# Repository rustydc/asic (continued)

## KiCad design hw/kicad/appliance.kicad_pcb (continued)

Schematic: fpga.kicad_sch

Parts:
J_BMC_NET: BMC Ethernet; RJ45_MAGJACK
J_HOST: SlimSAS 8i host cable; SLIMSAS_8I
J_SFP: SFP+ cage; SFP_CAGE
U_BMC: BMC SoC; BGA_BMC_21x21
U_CLK: Si5345; QFN64_9x9
U_FPGA: FPGA; FFVB676_26x26_P1.0

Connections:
BMC_ETH0_N: J_BMC_NET.2, U_BMC.2
BMC_ETH0_P: J_BMC_NET.1, U_BMC.1
BMC_ETH1_N: J_BMC_NET.4, U_BMC.4
BMC_ETH1_P: J_BMC_NET.3, U_BMC.3
BMC_ETH2_N: J_BMC_NET.6, U_BMC.6
BMC_ETH2_P: J_BMC_NET.5, U_BMC.5
BMC_ETH3_N: J_BMC_NET.8, U_BMC.8
BMC_ETH3_P: J_BMC_NET.7, U_BMC.7
DDR4_ADDR_CMD0: U_FPGA.D11; also elsewhere on the board
DDR4_ADDR_CMD1: U_FPGA.D12; also elsewhere on the board
DDR4_ADDR_CMD2: U_FPGA.D13; also elsewhere on the board
DDR4_ADDR_CMD3: U_FPGA.D14; also elsewhere on the board
DDR4_ADDR_CMD4: U_FPGA.D15; also elsewhere on the board
DDR4_ADDR_CMD5: U_FPGA.D16; also elsewhere on the board
DDR4_ADDR_CMD6: U_FPGA.D17; also elsewhere on the board
DDR4_ADDR_CMD7: U_FPGA.D18; also elsewhere on the board
DDR4_ADDR_CMD8: U_FPGA.D19; also elsewhere on the board
DDR4_ADDR_CMD9: U_FPGA.D20; also elsewhere on the board
DDR4_ADDR_CMD10: U_FPGA.D21; also elsewhere on the board
DDR4_ADDR_CMD11: U_FPGA.D22; also elsewhere on the board
DDR4_ADDR_CMD12: U_FPGA.D23; also elsewhere on the board
DDR4_ADDR_CMD13: U_FPGA.D24; also elsewhere on the board
DDR4_ADDR_CMD14: U_FPGA.D25; also elsewhere on the board
DDR4_ADDR_CMD15: U_FPGA.D26; also elsewhere on the board
DDR4_ADDR_CMD16: U_FPGA.E3; also elsewhere on the board
DDR4_ADDR_CMD17: U_FPGA.E4; also elsewhere on the board
DDR4_ADDR_CMD18: U_FPGA.E5; also elsewhere on the board
DDR4_ADDR_CMD19: U_FPGA.E6; also elsewhere on the board
DDR4_ADDR_CMD20: U_FPGA.E7; also elsewhere on the board
DDR4_ADDR_CMD21: U_FPGA.E8; also elsewhere on the board
DDR4_ADDR_CMD22: U_FPGA.E9; also elsewhere on the board
DDR4_ADDR_CMD23: U_FPGA.E10; also elsewhere on the board
DDR4_ADDR_CMD24: U_FPGA.E11; also elsewhere on the board
DDR4_ADDR_CMD25: U_FPGA.E12; also elsewhere on the board
DDR4_ADDR_CMD26: U_FPGA.E13; also elsewhere on the board
DDR4_ADDR_CMD27: U_FPGA.E14; also elsewhere on the board
DDR4_CK_N: U_FPGA.E16; also elsewhere on the board
DDR4_CK_P: U_FPGA.E15; also elsewhere on the board
DDR4_CTRL0: U_FPGA.E17; also elsewhere on the board
DDR4_CTRL1: U_FPGA.E18; also elsewhere on the board
DDR4_CTRL2: U_FPGA.E19; also elsewhere on the board
DDR4_CTRL3: U_FPGA.E20; also elsewhere on the board
DDR4_CTRL4: U_FPGA.E21; also elsewhere on the board
DDR4_CTRL5: U_FPGA.E22; also elsewhere on the board
DDR4_DM0: U_FPGA.D3; also elsewhere on the board
DDR4_DM1: U_FPGA.D4; also elsewhere on the board
DDR4_DM2: U_FPGA.D5; also elsewhere on the board
DDR4_DM3: U_FPGA.D6; also elsewhere on the board
DDR4_DM4: U_FPGA.D7; also elsewhere on the board
DDR4_DM5: U_FPGA.D8; also elsewhere on the board
DDR4_DM6: U_FPGA.D9; also elsewhere on the board
DDR4_DM7: U_FPGA.D10; also elsewhere on the board
DDR4_DQ0: U_FPGA.A1; also elsewhere on the board
DDR4_DQ1: U_FPGA.A2; also elsewhere on the board
DDR4_DQ2: U_FPGA.A3; also elsewhere on the board
DDR4_DQ3: U_FPGA.A4; also elsewhere on the board
DDR4_DQ4: U_FPGA.A5; also elsewhere on the board
DDR4_DQ5: U_FPGA.A6; also elsewhere on the board
DDR4_DQ6: U_FPGA.A7; also elsewhere on the board
DDR4_DQ7: U_FPGA.A8; also elsewhere on the board
DDR4_DQ8: U_FPGA.A9; also elsewhere on the board
DDR4_DQ9: U_FPGA.A10; also elsewhere on the board
DDR4_DQ10: U_FPGA.A11; also elsewhere on the board
DDR4_DQ11: U_FPGA.A12; also elsewhere on the board
DDR4_DQ12: U_FPGA.A13; also elsewhere on the board
DDR4_DQ13: U_FPGA.A14; also elsewhere on the board
DDR4_DQ14: U_FPGA.A15; also elsewhere on the board
DDR4_DQ15: U_FPGA.A16; also elsewhere on the board
DDR4_DQ16: U_FPGA.A17; also elsewhere on the board
DDR4_DQ17: U_FPGA.A18; also elsewhere on the board
DDR4_DQ18: U_FPGA.A19; also elsewhere on the board
DDR4_DQ19: U_FPGA.A20; also elsewhere on the board
DDR4_DQ20: U_FPGA.A21; also elsewhere on the board
DDR4_DQ21: U_FPGA.A22; also elsewhere on the board
DDR4_DQ22: U_FPGA.A23; also elsewhere on the board
DDR4_DQ23: U_FPGA.A24; also elsewhere on the board
DDR4_DQ24: U_FPGA.A25; also elsewhere on the board
DDR4_DQ25: U_FPGA.A26; also elsewhere on the board
DDR4_DQ26: U_FPGA.B1; also elsewhere on the board
DDR4_DQ27: U_FPGA.B2; also elsewhere on the board
DDR4_DQ28: U_FPGA.B3; also elsewhere on the board
DDR4_DQ29: U_FPGA.B4; also elsewhere on the board
DDR4_DQ30: U_FPGA.B5; also elsewhere on the board
DDR4_DQ31: U_FPGA.B6; also elsewhere on the board
DDR4_DQ32: U_FPGA.B7; also elsewhere on the board
DDR4_DQ33: U_FPGA.B8; also elsewhere on the board
DDR4_DQ34: U_FPGA.B9; also elsewhere on the board
DDR4_DQ35: U_FPGA.B10; also elsewhere on the board
DDR4_DQ36: U_FPGA.B11; also elsewhere on the board
DDR4_DQ37: U_FPGA.B12; also elsewhere on the board
DDR4_DQ38: U_FPGA.B13; also elsewhere on the board
DDR4_DQ39: U_FPGA.B14; also elsewhere on the board
DDR4_DQ40: U_FPGA.B15; also elsewhere on the board
DDR4_DQ41: U_FPGA.B16; also elsewhere on the board
DDR4_DQ42: U_FPGA.B17; also elsewhere on the board
DDR4_DQ43: U_FPGA.B18; also elsewhere on the board
DDR4_DQ44: U_FPGA.B19; also elsewhere on the board
DDR4_DQ45: U_FPGA.B20; also elsewhere on the board
DDR4_DQ46: U_FPGA.B21; also elsewhere on the board
DDR4_DQ47: U_FPGA.B22; also elsewhere on the board
DDR4_DQ48: U_FPGA.B23; also elsewhere on the board
DDR4_DQ49: U_FPGA.B24; also elsewhere on the board
DDR4_DQ50: U_FPGA.B25; also elsewhere on the board
DDR4_DQ51: U_FPGA.B26; also elsewhere on the board
DDR4_DQ52: U_FPGA.C1; also elsewhere on the board
DDR4_DQ53: U_FPGA.C2; also elsewhere on the board
DDR4_DQ54: U_FPGA.C3; also elsewhere on the board
DDR4_DQ55: U_FPGA.C4; also elsewhere on the board
DDR4_DQ56: U_FPGA.C5; also elsewhere on the board
DDR4_DQ57: U_FPGA.C6; also elsewhere on the board
DDR4_DQ58: U_FPGA.C7; also elsewhere on the board
DDR4_DQ59: U_FPGA.C8; also elsewhere on the board
DDR4_DQ60: U_FPGA.C9; also elsewhere on the board
DDR4_DQ61: U_FPGA.C10; also elsewhere on the board
DDR4_DQ62: U_FPGA.C11; also elsewhere on the board
DDR4_DQ63: U_FPGA.C12; also elsewhere on the board
DDR4_DQS0_N: U_FPGA.C14; also elsewhere on the board
DDR4_DQS0_P: U_FPGA.C13; also elsewhere on the board
DDR4_DQS1_N: U_FPGA.C16; also elsewhere on the board
DDR4_DQS1_P: U_FPGA.C15; also elsewhere on the board
DDR4_DQS2_N: U_FPGA.C18; also elsewhere on the board
DDR4_DQS2_P: U_FPGA.C17; also elsewhere on the board
DDR4_DQS3_N: U_FPGA.C20; also elsewhere on the board
DDR4_DQS3_P: U_FPGA.C19; also elsewhere on the board
DDR4_DQS4_N: U_FPGA.C22; also elsewhere on the board
DDR4_DQS4_P: U_FPGA.C21; also elsewhere on the board
DDR4_DQS5_N: U_FPGA.C24; also elsewhere on the board
DDR4_DQS5_P: U_FPGA.C23; also elsewhere on the board
DDR4_DQS6_N: U_FPGA.C26; also elsewhere on the board
DDR4_DQS6_P: U_FPGA.C25; also elsewhere on the board
DDR4_DQS7_N: U_FPGA.D2; also elsewhere on the board
DDR4_DQS7_P: U_FPGA.D1; also elsewhere on the board
FAN_0_PWM: U_BMC.9; also elsewhere on the board
FAN_0_TACH: U_BMC.10; also elsewhere on the board
FAN_1_PWM: U_BMC.11; also elsewhere on the board
FAN_1_TACH: U_BMC.12; also elsewhere on the board
FAN_2_PWM: U_BMC.13; also elsewhere on the board
FAN_2_TACH: U_BMC.14; also elsewhere on the board
FAN_3_PWM: U_BMC.15; also elsewhere on the board
FAN_3_TACH: U_BMC.16; also elsewhere on the board
FAN_4_PWM: U_BMC.17; also elsewhere on the board
FAN_4_TACH: U_BMC.18; also elsewhere on the board
FAN_5_PWM: U_BMC.19; also elsewhere on the board
FAN_5_TACH: U_BMC.20; also elsewhere on the board
GND: J_BMC_NET.10, J_BMC_NET.11, J_BMC_NET.12, J_HOST.37, J_HOST.38, J_HOST.39, J_HOST.40, J_HOST.41, J_HOST.42, J_HOST.43, J_HOST.44, J_HOST.45, J_HOST.46, J_HOST.47, J_HOST.48, J_HOST.49, J_HOST.50, J_HOST.51, J_HOST.52, J_HOST.53, J_HOST.54, J_SFP.13, J_SFP.14, J_SFP.15, J_SFP.16, U_BMC.28, U_BMC.29, U_CLK.2, U_FPGA.AA3, U_FPGA.AA5, U_FPGA.AA7, U_FPGA.AA9, U_FPGA.AA11, U_FPGA.AA13, U_FPGA.AA15, U_FPGA.AA17, U_FPGA.AA19, U_FPGA.AA21, U_FPGA.AA23, U_FPGA.AB4, U_FPGA.AB6, U_FPGA.AB8, U_FPGA.AB10, U_FPGA.AB12, U_FPGA.AB14, U_FPGA.AB16, U_FPGA.AB18, U_FPGA.AB20, U_FPGA.AB22, U_FPGA.AB24, U_FPGA.AC25, U_FPGA.AD26, U_FPGA.AE1, U_FPGA.AE17, U_FPGA.AE19, U_FPGA.AE21, U_FPGA.AE23, U_FPGA.AE25, U_FPGA.AF2, U_FPGA.AF26, U_FPGA.E23, U_FPGA.F4, U_FPGA.F6, U_FPGA.F8, U_FPGA.F10, U_FPGA.F12, U_FPGA.F14, U_FPGA.F16, U_FPGA.F18, U_FPGA.F20, U_FPGA.F22, U_FPGA.F24, U_FPGA.G3, U_FPGA.G5, U_FPGA.G7, U_FPGA.G9, U_FPGA.G11, U_FPGA.G13, U_FPGA.G15, U_FPGA.G17, U_FPGA.G19, U_FPGA.G21, U_FPGA.G23, U_FPGA.H4, U_FPGA.H6, U_FPGA.H8, U_FPGA.H10, U_FPGA.H12, U_FPGA.H14, U_FPGA.H16, U_FPGA.H18, U_FPGA.H20, U_FPGA.H22, U_FPGA.H24, U_FPGA.J3, U_FPGA.J5, U_FPGA.J7, U_FPGA.J9, U_FPGA.J11, U_FPGA.J13, U_FPGA.J15, U_FPGA.J17, U_FPGA.J19, U_FPGA.J21, U_FPGA.J23, U_FPGA.K4, U_FPGA.K6, U_FPGA.K8, U_FPGA.K10, U_FPGA.K12, U_FPGA.K14, U_FPGA.K16, U_FPGA.K18, U_FPGA.K20, U_FPGA.K22, U_FPGA.K24, U_FPGA.L3, U_FPGA.L5, U_FPGA.L7, U_FPGA.L9, U_FPGA.L11, U_FPGA.L13, U_FPGA.L15, U_FPGA.L17, U_FPGA.L19, U_FPGA.L21, U_FPGA.L23, U_FPGA.M4, U_FPGA.M6, U_FPGA.M8, U_FPGA.M10, U_FPGA.M12, U_FPGA.M14, U_FPGA.M16, U_FPGA.M18, U_FPGA.M20, U_FPGA.M22, U_FPGA.M24, U_FPGA.N3, U_FPGA.N5, U_FPGA.N7, U_FPGA.N9, U_FPGA.N11, U_FPGA.N13, U_FPGA.N15, U_FPGA.N17, U_FPGA.N19, U_FPGA.N21, U_FPGA.N23, U_FPGA.P4, U_FPGA.P6, U_FPGA.P8, U_FPGA.P10, U_FPGA.P12, U_FPGA.P14, U_FPGA.P16, U_FPGA.P18, U_FPGA.P20, U_FPGA.P22, U_FPGA.P24, U_FPGA.R3, U_FPGA.R5, U_FPGA.R7, U_FPGA.R9, U_FPGA.R11, U_FPGA.R13, U_FPGA.R15, U_FPGA.R17, U_FPGA.R19, U_FPGA.R21, U_FPGA.R23, U_FPGA.T4, U_FPGA.T6, U_FPGA.T8, U_FPGA.T10, U_FPGA.T12, U_FPGA.T14, U_FPGA.T16, U_FPGA.T18, U_FPGA.T20, U_FPGA.T22, U_FPGA.T24, U_FPGA.U3, U_FPGA.U5, U_FPGA.U7, U_FPGA.U9, U_FPGA.U11, U_FPGA.U13, U_FPGA.U15, U_FPGA.U17, U_FPGA.U19, U_FPGA.U21, U_FPGA.U23, U_FPGA.V4, U_FPGA.V6, U_FPGA.V8, U_FPGA.V10, U_FPGA.V12, U_FPGA.V14, U_FPGA.V16, U_FPGA.V18, U_FPGA.V20, U_FPGA.V22, U_FPGA.V24, U_FPGA.W3, U_FPGA.W5, U_FPGA.W7, U_FPGA.W9, U_FPGA.W11, U_FPGA.W13, U_FPGA.W15, U_FPGA.W17, U_FPGA.W19, U_FPGA.W21, U_FPGA.W23, U_FPGA.Y4, U_FPGA.Y6, U_FPGA.Y8, U_FPGA.Y10, U_FPGA.Y12, U_FPGA.Y14, U_FPGA.Y16, U_FPGA.Y18, U_FPGA.Y20, U_FPGA.Y22, U_FPGA.Y24; also elsewhere on the board
JTAG_TCK: U_FPGA.AC24; also elsewhere on the board
JTAG_TDI_FPGA: U_FPGA.AD2
JTAG_TDO_FPGA: U_FPGA.AD3; also elsewhere on the board
JTAG_TMS: U_FPGA.AD1; also elsewhere on the board
JTAG_TRST: U_FPGA.AD4; also elsewhere on the board
LINK0_CLOCK: U_FPGA.AA26; also elsewhere on the board
LINK0_DATA0: U_FPGA.E26; also elsewhere on the board
LINK0_DATA1: U_FPGA.E25; also elsewhere on the board
LINK0_DATA2: U_FPGA.F26; also elsewhere on the board
LINK0_DATA3: U_FPGA.F25; also elsewhere on the board
LINK0_DATA4: U_FPGA.G26; also elsewhere on the board
LINK0_DATA5: U_FPGA.G25; also elsewhere on the board
LINK0_DATA6: U_FPGA.H26; also elsewhere on the board
LINK0_DATA7: U_FPGA.H25; also elsewhere on the board
LINK0_DATA8: U_FPGA.J26; also elsewhere on the board
LINK0_DATA9: U_FPGA.J25; also elsewhere on the board
LINK0_DATA10: U_FPGA.K26; also elsewhere on the board
LINK0_DATA11: U_FPGA.K25; also elsewhere on the board
LINK0_DATA12: U_FPGA.L26; also elsewhere on the board
LINK0_DATA13: U_FPGA.L25; also elsewhere on the board
LINK0_DATA14: U_FPGA.M26; also elsewhere on the board
LINK0_DATA15: U_FPGA.M25; also elsewhere on the board
LINK0_DATA16: U_FPGA.N26; also elsewhere on the board
LINK0_DATA17: U_FPGA.N25; also elsewhere on the board
LINK0_DATA18: U_FPGA.P26; also elsewhere on the board
LINK0_DATA19: U_FPGA.P25; also elsewhere on the board
LINK0_DATA20: U_FPGA.R26; also elsewhere on the board
LINK0_DATA21: U_FPGA.R25; also elsewhere on the board
LINK0_DATA22: U_FPGA.T26; also elsewhere on the board
LINK0_DATA23: U_FPGA.T25; also elsewhere on the board
LINK0_DATA24: U_FPGA.U26; also elsewhere on the board
LINK0_DATA25: U_FPGA.U25; also elsewhere on the board
LINK0_DATA26: U_FPGA.V26; also elsewhere on the board
LINK0_DATA27: U_FPGA.V25; also elsewhere on the board
LINK0_DATA28: U_FPGA.W26; also elsewhere on the board
LINK0_DATA29: U_FPGA.W25; also elsewhere on the board
LINK0_DATA30: U_FPGA.Y26; also elsewhere on the board
LINK0_DATA31: U_FPGA.Y25; also elsewhere on the board
LINK0_READY_BACK: U_FPGA.AB26; also elsewhere on the board
LINK0_SOF: U_FPGA.AB25; also elsewhere on the board
LINK0_VALID: U_FPGA.AA25; also elsewhere on the board
LINK10_CLOCK: U_FPGA.AA1; also elsewhere on the board
LINK10_DATA0: U_FPGA.E1; also elsewhere on the board
LINK10_DATA1: U_FPGA.E2; also elsewhere on the board
LINK10_DATA2: U_FPGA.F1; also elsewhere on the board
LINK10_DATA3: U_FPGA.F2; also elsewhere on the board
LINK10_DATA4: U_FPGA.G1; also elsewhere on the board
LINK10_DATA5: U_FPGA.G2; also elsewhere on the board
LINK10_DATA6: U_FPGA.H1; also elsewhere on the board
LINK10_DATA7: U_FPGA.H2; also elsewhere on the board
LINK10_DATA8: U_FPGA.J1; also elsewhere on the board
LINK10_DATA9: U_FPGA.J2; also elsewhere on the board
LINK10_DATA10: U_FPGA.K1; also elsewhere on the board
LINK10_DATA11: U_FPGA.K2; also elsewhere on the board
LINK10_DATA12: U_FPGA.L1; also elsewhere on the board
LINK10_DATA13: U_FPGA.L2; also elsewhere on the board
LINK10_DATA14: U_FPGA.M1; also elsewhere on the board
LINK10_DATA15: U_FPGA.M2; also elsewhere on the board
LINK10_DATA16: U_FPGA.N1; also elsewhere on the board
LINK10_DATA17: U_FPGA.N2; also elsewhere on the board
LINK10_DATA18: U_FPGA.P1; also elsewhere on the board
LINK10_DATA19: U_FPGA.P2; also elsewhere on the board
LINK10_DATA20: U_FPGA.R1; also elsewhere on the board
LINK10_DATA21: U_FPGA.R2; also elsewhere on the board
LINK10_DATA22: U_FPGA.T1; also elsewhere on the board
LINK10_DATA23: U_FPGA.T2; also elsewhere on the board
LINK10_DATA24: U_FPGA.U1; also elsewhere on the board
LINK10_DATA25: U_FPGA.U2; also elsewhere on the board
LINK10_DATA26: U_FPGA.V1; also elsewhere on the board
LINK10_DATA27: U_FPGA.V2; also elsewhere on the board
LINK10_DATA28: U_FPGA.W1; also elsewhere on the board
LINK10_DATA29: U_FPGA.W2; also elsewhere on the board
LINK10_DATA30: U_FPGA.Y1; also elsewhere on the board
LINK10_DATA31: U_FPGA.Y2; also elsewhere on the board
LINK10_READY_BACK: U_FPGA.AB1; also elsewhere on the board
LINK10_SOF: U_FPGA.AB2; also elsewhere on the board
LINK10_VALID: U_FPGA.AA2; also elsewhere on the board
MGMT_CS_A0: U_FPGA.AC4; also elsewhere on the board
MGMT_CS_A1: U_FPGA.AC6; also elsewhere on the board
MGMT_CS_A2: U_FPGA.AC8; also elsewhere on the board
MGMT_CS_A3: U_FPGA.AC10; also elsewhere on the board
MGMT_CS_A4: U_FPGA.AC12; also elsewhere on the board
MGMT_CS_A5: U_FPGA.AC14; also elsewhere on the board
MGMT_CS_A6: U_FPGA.AC16; also elsewhere on the board
MGMT_CS_A7: U_FPGA.AC18; also elsewhere on the board
MGMT_CS_H0: U_FPGA.AC20; also elsewhere on the board
MGMT_CS_H1: U_FPGA.AC22; also elsewhere on the board
MGMT_IRQ_A0: U_FPGA.AC5; also elsewhere on the board
MGMT_IRQ_A1: U_FPGA.AC7; also elsewhere on the board
MGMT_IRQ_A2: U_FPGA.AC9; also elsewhere on the board
MGMT_IRQ_A3: U_FPGA.AC11; also elsewhere on the board
MGMT_IRQ_A4: U_FPGA.AC13; also elsewhere on the board
MGMT_IRQ_A5: U_FPGA.AC15; also elsewhere on the board
MGMT_IRQ_A6: U_FPGA.AC17; also elsewhere on the board
MGMT_IRQ_A7: U_FPGA.AC19; also elsewhere on the board
MGMT_IRQ_H0: U_FPGA.AC21; also elsewhere on the board
MGMT_IRQ_H1: U_FPGA.AC23; also elsewhere on the board
MGMT_MISO: U_FPGA.AC3; also elsewhere on the board
MGMT_MOSI: U_FPGA.AC2; also elsewhere on the board
MGMT_SCLK: U_FPGA.AC1; also elsewhere on the board
MGTAVCC: U_FPGA.AB5, U_FPGA.AE24, U_FPGA.G24, U_FPGA.N14, U_FPGA.T21; also elsewhere on the board
MGTAVTT: U_FPGA.AB11, U_FPGA.K7, U_FPGA.N20, U_FPGA.W4; also elsewhere on the board
PCIE_PERST: J_HOST.35, U_FPGA.AE15
PCIE_REFCLK_N: J_HOST.34, U_FPGA.AE14
PCIE_REFCLK_P: J_HOST.33, U_FPGA.AE13
PCIE_RX0_N: J_HOST.18, U_FPGA.AF20
PCIE_RX0_P: J_HOST.17, U_FPGA.AF19
PCIE_RX1_N: J_HOST.20, U_FPGA.AF22
PCIE_RX1_P: J_HOST.19, U_FPGA.AF21
PCIE_RX2_N: J_HOST.22, U_FPGA.AF24
PCIE_RX2_P: J_HOST.21, U_FPGA.AF23
PCIE_RX3_N: J_HOST.24, U_FPGA.AE4
PCIE_RX3_P: J_HOST.23, U_FPGA.AE3
PCIE_RX4_N: J_HOST.26, U_FPGA.AE6
PCIE_RX4_P: J_HOST.25, U_FPGA.AE5
PCIE_RX5_N: J_HOST.28, U_FPGA.AE8
PCIE_RX5_P: J_HOST.27, U_FPGA.AE7
PCIE_RX6_N: J_HOST.30, U_FPGA.AE10
PCIE_RX6_P: J_HOST.29, U_FPGA.AE9
PCIE_RX7_N: J_HOST.32, U_FPGA.AE12
PCIE_RX7_P: J_HOST.31, U_FPGA.AE11
PCIE_TX0_N: J_HOST.2, U_FPGA.AF4
PCIE_TX0_P: J_HOST.1, U_FPGA.AF3
PCIE_TX1_N: J_HOST.4, U_FPGA.AF6
PCIE_TX1_P: J_HOST.3, U_FPGA.AF5
PCIE_TX2_N: J_HOST.6, U_FPGA.AF8
PCIE_TX2_P: J_HOST.5, U_FPGA.AF7
PCIE_TX3_N: J_HOST.8, U_FPGA.AF10
PCIE_TX3_P: J_HOST.7, U_FPGA.AF9
PCIE_TX4_N: J_HOST.10, U_FPGA.AF12
PCIE_TX4_P: J_HOST.9, U_FPGA.AF11
PCIE_TX5_N: J_HOST.12, U_FPGA.AF14
PCIE_TX5_P: J_HOST.11, U_FPGA.AF13
PCIE_TX6_N: J_HOST.14, U_FPGA.AF16
PCIE_TX6_P: J_HOST.13, U_FPGA.AF15
PCIE_TX7_N: J_HOST.16, U_FPGA.AF18
PCIE_TX7_P: J_HOST.15, U_FPGA.AF17
PCIE_WAKE: J_HOST.36, U_FPGA.AE16
PMB_SCL: U_BMC.23; also elsewhere on the board
PMB_SDA: U_BMC.24; also elsewhere on the board
PSU_ON: U_BMC.25; also elsewhere on the board
QSPI0: U_FPGA.AD17
QSPI1: U_FPGA.AD18
QSPI2: U_FPGA.AD19
QSPI3: U_FPGA.AD20
QSPI4: U_FPGA.AD21
QSPI5: U_FPGA.AD22
REFCLK_A0_N: U_CLK.6; also elsewhere on the board
REFCLK_A0_P: U_CLK.5; also elsewhere on the board
REFCLK_A1_N: U_CLK.8; also elsewhere on the board
REFCLK_A1_P: U_CLK.7; also elsewhere on the board
REFCLK_A2_N: U_CLK.10; also elsewhere on the board
REFCLK_A2_P: U_CLK.9; also elsewhere on the board
REFCLK_A3_N: U_CLK.12; also elsewhere on the board
REFCLK_A3_P: U_CLK.11; also elsewhere on the board
REFCLK_A4_N: U_CLK.14; also elsewhere on the board
REFCLK_A4_P: U_CLK.13; also elsewhere on the board
REFCLK_A5_N: U_CLK.16; also elsewhere on the board
REFCLK_A5_P: U_CLK.15; also elsewhere on the board
REFCLK_A6_N: U_CLK.18; also elsewhere on the board
REFCLK_A6_P: U_CLK.17; also elsewhere on the board
REFCLK_A7_N: U_CLK.20; also elsewhere on the board
REFCLK_A7_P: U_CLK.19; also elsewhere on the board
REFCLK_FPGA_N: U_CLK.4, U_FPGA.AD6
REFCLK_FPGA_P: U_CLK.3, U_FPGA.AD5
REFCLK_H0_N: U_CLK.22; also elsewhere on the board
REFCLK_H0_P: U_CLK.21; also elsewhere on the board
REFCLK_H1_N: U_CLK.24; also elsewhere on the board
REFCLK_H1_P: U_CLK.23; also elsewhere on the board
SFP_CTRL0: J_SFP.7, U_FPGA.AD13
SFP_CTRL1: J_SFP.8, U_FPGA.AD14
SFP_CTRL2: J_SFP.9, U_FPGA.AD15
SFP_CTRL3: J_SFP.10, U_FPGA.AD16
SFP_I2C0: J_SFP.5, U_FPGA.AD11
SFP_I2C1: J_SFP.6, U_FPGA.AD12
SFP_RX_N: J_SFP.4, U_FPGA.AD10
SFP_RX_P: J_SFP.3, U_FPGA.AD9
SFP_TX_N: J_SFP.2, U_FPGA.AD8
SFP_TX_P: J_SFP.1, U_FPGA.AD7
UART_RX: U_BMC.22, U_FPGA.AD24
UART_TX: U_BMC.21, U_FPGA.AD23
VCCAUX_1V8: U_FPGA.AB17, U_FPGA.G6, U_FPGA.K13, U_FPGA.T3, U_FPGA.W10; also elsewhere on the board
VCCINT_0V85: U_FPGA.AA4, U_FPGA.AA6, U_FPGA.AA8, U_FPGA.AA10, U_FPGA.AA12, U_FPGA.AA14, U_FPGA.AA16, U_FPGA.AA18, U_FPGA.AA20, U_FPGA.AA22, U_FPGA.AA24, U_FPGA.AB3, U_FPGA.AB7, U_FPGA.AB9, U_FPGA.AB13, U_FPGA.AB15, U_FPGA.AB19, U_FPGA.AB21, U_FPGA.AC26, U_FPGA.AD25, U_FPGA.AE2, U_FPGA.AE20, U_FPGA.AE22, U_FPGA.AE26, U_FPGA.AF1, U_FPGA.AF25, U_FPGA.E24, U_FPGA.F3, U_FPGA.F5, U_FPGA.F7, U_FPGA.F9, U_FPGA.F11, U_FPGA.F13, U_FPGA.F15, U_FPGA.F17, U_FPGA.F19, U_FPGA.F21, U_FPGA.F23, U_FPGA.G4, U_FPGA.G8, U_FPGA.G10, U_FPGA.G14, U_FPGA.G16, U_FPGA.G20, U_FPGA.G22, U_FPGA.H3, U_FPGA.H5, U_FPGA.H7, U_FPGA.H9, U_FPGA.H11, U_FPGA.H13, U_FPGA.H15, U_FPGA.H17, U_FPGA.H19, U_FPGA.H21, U_FPGA.H23, U_FPGA.J4, U_FPGA.J6, U_FPGA.J8, U_FPGA.J10, U_FPGA.J12, U_FPGA.J14, U_FPGA.J16, U_FPGA.J18, U_FPGA.J20, U_FPGA.J22, U_FPGA.J24, U_FPGA.K3, U_FPGA.K5, U_FPGA.K9, U_FPGA.K11, U_FPGA.K15, U_FPGA.K17, U_FPGA.K21, U_FPGA.K23, U_FPGA.L4, U_FPGA.L6, U_FPGA.L8, U_FPGA.L10, U_FPGA.L12, U_FPGA.L14, U_FPGA.L16, U_FPGA.L18, U_FPGA.L20, U_FPGA.L22, U_FPGA.L24, U_FPGA.M3, U_FPGA.M5, U_FPGA.M7, U_FPGA.M9, U_FPGA.M11, U_FPGA.M13, U_FPGA.M15, U_FPGA.M17, U_FPGA.M19, U_FPGA.M21, U_FPGA.M23, U_FPGA.N4, U_FPGA.N6, U_FPGA.N10, U_FPGA.N12, U_FPGA.N16, U_FPGA.N18, U_FPGA.N22, U_FPGA.N24, U_FPGA.P3, U_FPGA.P5, U_FPGA.P7, U_FPGA.P9, U_FPGA.P11, U_FPGA.P13, U_FPGA.P15, U_FPGA.P17, U_FPGA.P19, U_FPGA.P21, U_FPGA.P23, U_FPGA.R4, U_FPGA.R6, U_FPGA.R8, U_FPGA.R10, U_FPGA.R12, U_FPGA.R14, U_FPGA.R16, U_FPGA.R18, U_FPGA.R20, U_FPGA.R22, U_FPGA.R24, U_FPGA.T5, U_FPGA.T7, U_FPGA.T11, U_FPGA.T13, U_FPGA.T17, U_FPGA.T19, U_FPGA.T23, U_FPGA.U4, U_FPGA.U6, U_FPGA.U8, U_FPGA.U10, U_FPGA.U12, U_FPGA.U14, U_FPGA.U16, U_FPGA.U18, U_FPGA.U20, U_FPGA.U22, U_FPGA.U24, U_FPGA.V3, U_FPGA.V5, U_FPGA.V7, U_FPGA.V9, U_FPGA.V11, U_FPGA.V13, U_FPGA.V15, U_FPGA.V17, U_FPGA.V19, U_FPGA.V21, U_FPGA.V23, U_FPGA.W6, U_FPGA.W8, U_FPGA.W12, U_FPGA.W14, U_FPGA.W18, U_FPGA.W20, U_FPGA.W24, U_FPGA.Y3, U_FPGA.Y5, U_FPGA.Y7, U_FPGA.Y9, U_FPGA.Y11, U_FPGA.Y13, U_FPGA.Y15, U_FPGA.Y17, U_FPGA.Y19, U_FPGA.Y21, U_FPGA.Y23; also elsewhere on the board
VCCO_1V2: U_FPGA.AE18, U_FPGA.G18, U_FPGA.N8, U_FPGA.T15, U_FPGA.W22; also elsewhere on the board
VCCO_1V8: U_FPGA.AB23, U_FPGA.G12, U_FPGA.K19, U_FPGA.T9, U_FPGA.W16; also elsewhere on the board
VDD_3V3: J_BMC_NET.9, J_SFP.11, J_SFP.12, U_BMC.26, U_BMC.27; also elsewhere on the board
VDD_IO_1V8: U_CLK.1; also elsewhere on the board

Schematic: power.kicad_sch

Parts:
J_FAN0, J_FAN1, J_FAN2, J_FAN3, J_FAN4, J_FAN5: fan header; FAN_4PIN
J_PSU0, J_PSU1: CRPS 12 V output; CRPS_BLADES
REG_0V3: VDDQ_0V3 regulator; REG_MODULE_20x6
REG_0V9: VDD2L_0V9 regulator; REG_MODULE_20x6
REG_1V05: VDD2H_1V05 regulator; REG_MODULE_20x6
REG_1V8: VDD1_1V8 regulator; REG_MODULE_20x6
REG_3V3: VDD_3V3 regulator; REG_MODULE_20x6
REG_DDR: VDD_1V2, VPP_2V5 regulator; REG_MODULE_20x6
REG_FPGA: VCCINT_0V85, VCCAUX_1V8, VCCO_1V8, VCCO_1V2, MGTA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; REG_MODULE_20x6
REG_IO_1V8: VDD_IO_1V8 regulator; REG_MODULE_20x6
VRM_A0: core VRM VDD_CORE_A0; VRM_MODULE_26x6
VRM_A1: core VRM VDD_CORE_A1; VRM_MODULE_26x6
VRM_A2: core VRM VDD_CORE_A2; VRM_MODULE_26x6
VRM_A3: core VRM VDD_CORE_A3; VRM_MODULE_26x6
VRM_A4: core VRM VDD_CORE_A4; VRM_MODULE_26x6
VRM_A5: core VRM VDD_CORE_A5; VRM_MODULE_26x6
VRM_A6: core VRM VDD_CORE_A6; VRM_MODULE_26x6
VRM_A7: core VRM VDD_CORE_A7; VRM_MODULE_26x6
VRM_H0: core VRM VDD_CORE_H0; VRM_MODULE_26x6
VRM_H1: core VRM VDD_CORE_H1; VRM_MODULE_26x6

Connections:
+12V: J_FAN0.1, J_FAN1.1, J_FAN2.1, J_FAN3.1, J_FAN4.1, J_FAN5.1, J_PSU0.1, J_PSU0.2, J_PSU0.3, J_PSU0.4, J_PSU0.5, J_PSU0.6, J_PSU1.1, J_PSU1.2, J_PSU1.3, J_PSU1.4, J_PSU1.5, J_PSU1.6, REG_0V3.1, REG_0V3.2, REG_0V3.3, REG_0V9.1, REG_0V9.2, REG_0V9.3, REG_1V05.1, REG_1V05.2, REG_1V05.3, REG_1V8.1, REG_1V8.2, REG_1V8.3, REG_3V3.1, REG_3V3.2, REG_3V3.3, REG_DDR.1, REG_DDR.2, REG_DDR.3, REG_FPGA.1, REG_FPGA.2, REG_FPGA.3, REG_IO_1V8.1, REG_IO_1V8.2, REG_IO_1V8.3, VRM_A0.1, VRM_A0.2, VRM_A0.3, VRM_A0.4, VRM_A1.1, VRM_A1.2, VRM_A1.3, VRM_A1.4, VRM_A2.1, VRM_A2.2, VRM_A2.3, VRM_A2.4, VRM_A3.1, VRM_A3.2, VRM_A3.3, VRM_A3.4, VRM_A4.1, VRM_A4.2, VRM_A4.3, VRM_A4.4, VRM_A5.1, VRM_A5.2, VRM_A5.3, VRM_A5.4, VRM_A6.1, VRM_A6.2, VRM_A6.3, VRM_A6.4, VRM_A7.1, VRM_A7.2, VRM_A7.3, VRM_A7.4, VRM_H0.1, VRM_H0.2, VRM_H0.3, VRM_H0.4, VRM_H1.1, VRM_H1.2, VRM_H1.3, VRM_H1.4
FAN_0_PWM: J_FAN0.3; also elsewhere on the board
FAN_0_TACH: J_FAN0.4; also elsewhere on the board
FAN_1_PWM: J_FAN1.3; also elsewhere on the board
FAN_1_TACH: J_FAN1.4; also elsewhere on the board
FAN_2_PWM: J_FAN2.3; also elsewhere on the board
FAN_2_TACH: J_FAN2.4; also elsewhere on the board
FAN_3_PWM: J_FAN3.3; also elsewhere on the board
FAN_3_TACH: J_FAN3.4; also elsewhere on the board
FAN_4_PWM: J_FAN4.3; also elsewhere on the board
FAN_4_TACH: J_FAN4.4; also elsewhere on the board
FAN_5_PWM: J_FAN5.3; also elsewhere on the board
FAN_5_TACH: J_FAN5.4; also elsewhere on the board
GND: J_FAN0.2, J_FAN1.2, J_FAN2.2, J_FAN3.2, J_FAN4.2, J_FAN5.2, J_PSU0.7, J_PSU0.8, J_PSU0.9, J_PSU0.10, J_PSU0.11, J_PSU0.12, J_PSU0.16, J_PSU1.7, J_PSU1.8, J_PSU1.9, J_PSU1.10, J_PSU1.11, J_PSU1.12, J_PSU1.16, REG_0V3.7, REG_0V3.8, REG_0V3.9, REG_0V9.7, REG_0V9.8, REG_0V9.9, REG_1V05.7, REG_1V05.8, REG_1V05.9, REG_1V8.7, REG_1V8.8, REG_1V8.9, REG_3V3.7, REG_3V3.8, REG_3V3.9, REG_DDR.8, REG_DDR.9, REG_DDR.10, REG_FPGA.12, REG_FPGA.13, REG_FPGA.14, REG_IO_1V8.7, REG_IO_1V8.8, REG_IO_1V8.9, VRM_A0.11, VRM_A0.12, VRM_A0.13, VRM_A0.14, VRM_A0.15, VRM_A0.16, VRM_A1.11, VRM_A1.12, VRM_A1.13, VRM_A1.14, VRM_A1.15, VRM_A1.16, VRM_A2.11, VRM_A2.12, VRM_A2.13, VRM_A2.14, VRM_A2.15, VRM_A2.16, VRM_A3.11, VRM_A3.12, VRM_A3.13, VRM_A3.14, VRM_A3.15, VRM_A3.16, VRM_A4.11, VRM_A4.12, VRM_A4.13, VRM_A4.14, VRM_A4.15, VRM_A4.16, VRM_A5.11, VRM_A5.12, VRM_A5.13, VRM_A5.14, VRM_A5.15, VRM_A5.16, VRM_A6.11, VRM_A6.12, VRM_A6.13, VRM_A6.14, VRM_A6.15, VRM_A6.16, VRM_A7.11, VRM_A7.12, VRM_A7.13, VRM_A7.14, VRM_A7.15, VRM_A7.16, VRM_H0.11, VRM_H0.12, VRM_H0.13, VRM_H0.14, VRM_H0.15, VRM_H0.16, VRM_H1.11, VRM_H1.12, VRM_H1.13, VRM_H1.14, VRM_H1.15, VRM_H1.16; also elsewhere on the board
MGTAVCC: REG_FPGA.10; also elsewhere on the board
MGTAVTT: REG_FPGA.11; also elsewhere on the board
PMB_SCL: J_PSU0.13, J_PSU1.13, VRM_A0.17, VRM_A1.17, VRM_A2.17, VRM_A3.17, VRM_A4.17, VRM_A5.17, VRM_A6.17, VRM_A7.17, VRM_H0.17, VRM_H1.17; also elsewhere on the board
PMB_SDA: J_PSU0.14, J_PSU1.14, VRM_A0.18, VRM_A1.18, VRM_A2.18, VRM_A3.18, VRM_A4.18, VRM_A5.18, VRM_A6.18, VRM_A7.18, VRM_H0.18, VRM_H1.18; also elsewhere on the board
PSU_ON: J_PSU0.15, J_PSU1.15; also elsewhere on the board
VCCAUX_1V8: REG_FPGA.7; also elsewhere on the board
VCCINT_0V85: REG_FPGA.4, REG_FPGA.5, REG_FPGA.6; also elsewhere on the board
VCCO_1V2: REG_FPGA.9; also elsewhere on the board
VCCO_1V8: REG_FPGA.8; also elsewhere on the board
VDD1_1V8: REG_1V8.4, REG_1V8.5, REG_1V8.6; also elsewhere on the board
VDD2H_1V05: REG_1V05.4, REG_1V05.5, REG_1V05.6; also elsewhere on the board
VDD2L_0V9: REG_0V9.4, REG_0V9.5, REG_0V9.6; also elsewhere on the board
VDDQ_0V3: REG_0V3.4, REG_0V3.5, REG_0V3.6; also elsewhere on the board
VDD_1V2: REG_DDR.4, REG_DDR.5, REG_DDR.6; also elsewhere on the board
VDD_3V3: REG_3V3.4, REG_3V3.5, REG_3V3.6; also elsewhere on the board
VDD_CORE_A0: VRM_A0.5, VRM_A0.6, VRM_A0.7, VRM_A0.8, VRM_A0.9, VRM_A0.10; also elsewhere on the board
VDD_CORE_A1: VRM_A1.5, VRM_A1.6, VRM_A1.7, VRM_A1.8, VRM_A1.9, VRM_A1.10; also elsewhere on the board
VDD_CORE_A2: VRM_A2.5, VRM_A2.6, VRM_A2.7, VRM_A2.8, VRM_A2.9, VRM_A2.10; also elsewhere on the board
VDD_CORE_A3: VRM_A3.5, VRM_A3.6, VRM_A3.7, VRM_A3.8, VRM_A3.9, VRM_A3.10; also elsewhere on the board
VDD_CORE_A4: VRM_A4.5, VRM_A4.6, VRM_A4.7, VRM_A4.8, VRM_A4.9, VRM_A4.10; also elsewhere on the board
VDD_CORE_A5: VRM_A5.5, VRM_A5.6, VRM_A5.7, VRM_A5.8, VRM_A5.9, VRM_A5.10; also elsewhere on the board
VDD_CORE_A6: VRM_A6.5, VRM_A6.6, VRM_A6.7, VRM_A6.8, VRM_A6.9, VRM_A6.10; also elsewhere on the board
VDD_CORE_A7: VRM_A7.5, VRM_A7.6, VRM_A7.7, VRM_A7.8, VRM_A7.9, VRM_A7.10; also elsewhere on the board
VDD_CORE_H0: VRM_H0.5, VRM_H0.6, VRM_H0.7, VRM_H0.8, VRM_H0.9, VRM_H0.10; also elsewhere on the board
VDD_CORE_H1: VRM_H1.5, VRM_H1.6, VRM_H1.7, VRM_H1.8, VRM_H1.9, VRM_H1.10; also elsewhere on the board
VDD_IO_1V8: REG_IO_1V8.4, REG_IO_1V8.5, REG_IO_1V8.6; also elsewhere on the board
VPP_2V5: REG_DDR.7; also elsewhere on the board
VRM_EN_A0: VRM_A0.19
VRM_EN_A1: VRM_A1.19
VRM_EN_A2: VRM_A2.19
VRM_EN_A3: VRM_A3.19
VRM_EN_A4: VRM_A4.19
VRM_EN_A5: VRM_A5.19
VRM_EN_A6: VRM_A6.19
VRM_EN_A7: VRM_A7.19
VRM_EN_H0: VRM_H0.19
VRM_EN_H1: VRM_H1.19

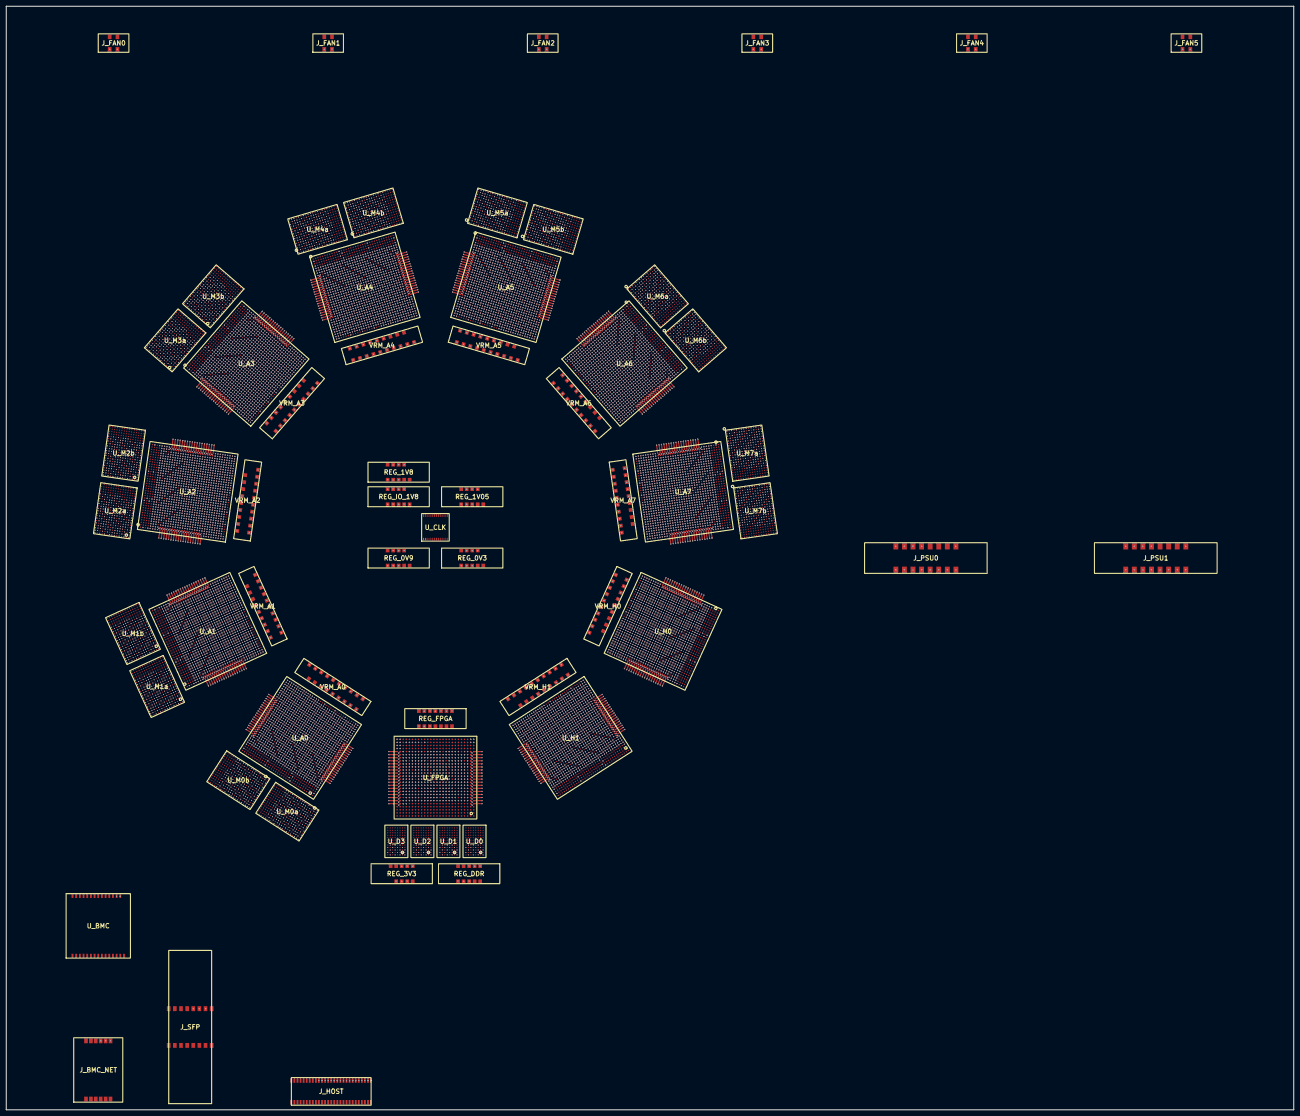
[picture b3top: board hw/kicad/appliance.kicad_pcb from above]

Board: 12 copper layers, 420.0 x 360.0 mm, 62 parts (0 on the bottom side), 1716 nets.
